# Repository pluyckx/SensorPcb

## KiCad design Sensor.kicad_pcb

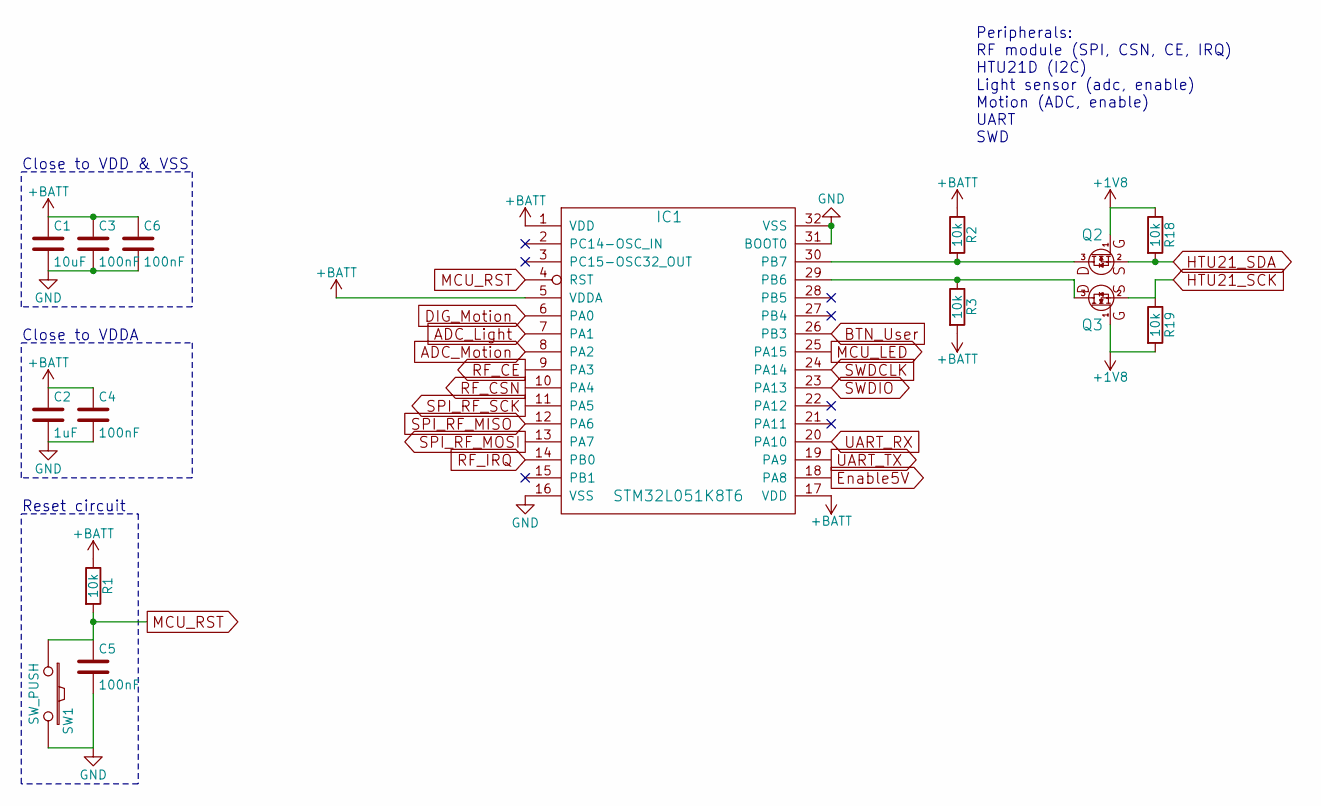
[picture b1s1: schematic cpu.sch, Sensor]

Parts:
C1: 10uF; R_0805
C2: 1uF; R_0805
C3, C4, C5, C6: 100nF; R_0805
IC1: STM32L051K8T6; STM32L051-LQFP32
Q2, Q3: NMosfetGen; SOT23
R1, R2, R3, R18, R19: 10k; R_0603
SW1: SW_PUSH; MicroSwitch_6x6mm

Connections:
+1V8: Q2.1, Q3.1, R18.1, R19.2; also elsewhere on the board
+BATT: C1.1, C2.1, C3.1, C4.1, C6.1, IC1.1 (VDD), IC1.5 (VDDA), IC1.17 (VDD), R1.1, R2.1, R3.2; also elsewhere on the board
ADC_Light: IC1.7 (PA1); also elsewhere on the board
ADC_Motion: IC1.8 (PA2); also elsewhere on the board
BTN_User: IC1.26 (PB3); also elsewhere on the board
DIG_Motion: IC1.6 (PA0); also elsewhere on the board
Enable5V: IC1.18 (PA8); also elsewhere on the board
GND: C1.2, C2.2, C3.2, C4.2, C5.2, C6.2, IC1.16 (VSS), IC1.31 (BOOT0), IC1.32 (VSS), SW1.2; also elsewhere on the board
HTU21_SCK: Q3.2, R19.1; also elsewhere on the board
HTU21_SDA: Q2.2, R18.2; also elsewhere on the board
MCU_LED: IC1.25 (PA15); also elsewhere on the board
MCU_RST: C5.1, IC1.4 (RST), R1.2, SW1.1; also elsewhere on the board
unnamed: IC1.29 (PB6), Q3.3, R3.1
unnamed: IC1.30 (PB7), Q2.3, R2.2
RF_CE: IC1.9 (PA3); also elsewhere on the board
RF_CSN: IC1.10 (PA4); also elsewhere on the board
RF_IRQ: IC1.14 (PB0); also elsewhere on the board
SPI_RF_MISO: IC1.12 (PA6); also elsewhere on the board
SPI_RF_MOSI: IC1.13 (PA7); also elsewhere on the board
SPI_RF_SCK: IC1.11 (PA5); also elsewhere on the board
SWDCLK: IC1.24 (PA14); also elsewhere on the board
SWDIO: IC1.23 (PA13); also elsewhere on the board
UART_RX: IC1.20 (PA10); also elsewhere on the board
UART_TX: IC1.19 (PA9); also elsewhere on the board

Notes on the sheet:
Close to VDD & VSS
Close to VDDA
Reset circuit
Peripherals: RF module (SPI, CSN, CE, IRQ) HTU21D (I2C) Light sensor (adc, enable) Motion (ADC, enable) UART SWD

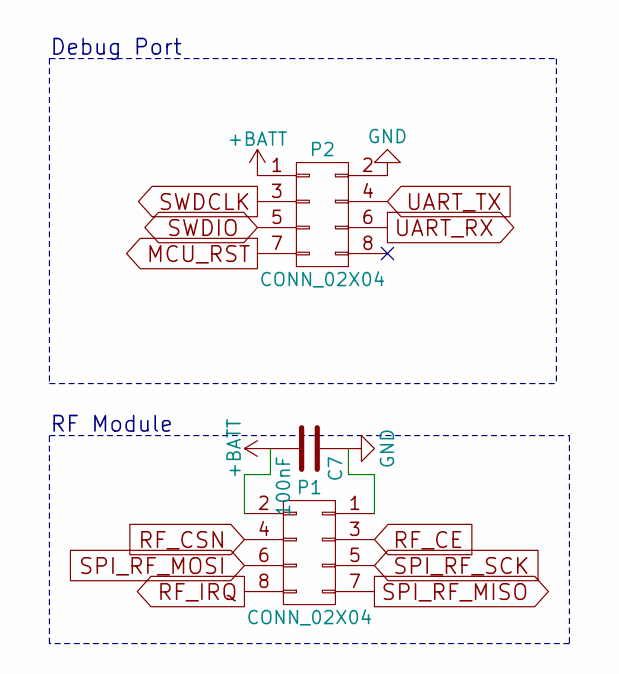
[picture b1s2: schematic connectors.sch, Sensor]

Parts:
C7: 100nF; R_0805
P1: CONN_02X04; Pin_Header_Straight_2x04_SMD
P2: CONN_02X04; Pin_Header_Straight_2x04_TH

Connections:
+BATT: C7.2, P1.2, P2.1; also elsewhere on the board
GND: C7.1, P1.1, P2.2; also elsewhere on the board
MCU_RST: P2.7; also elsewhere on the board
RF_CE: P1.3; also elsewhere on the board
RF_CSN: P1.4; also elsewhere on the board
RF_IRQ: P1.8; also elsewhere on the board
SPI_RF_MISO: P1.7; also elsewhere on the board
SPI_RF_MOSI: P1.6; also elsewhere on the board
SPI_RF_SCK: P1.5; also elsewhere on the board
SWDCLK: P2.3; also elsewhere on the board
SWDIO: P2.5; also elsewhere on the board
UART_RX: P2.6; also elsewhere on the board
UART_TX: P2.4; also elsewhere on the board

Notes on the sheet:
RF Module
Debug Port

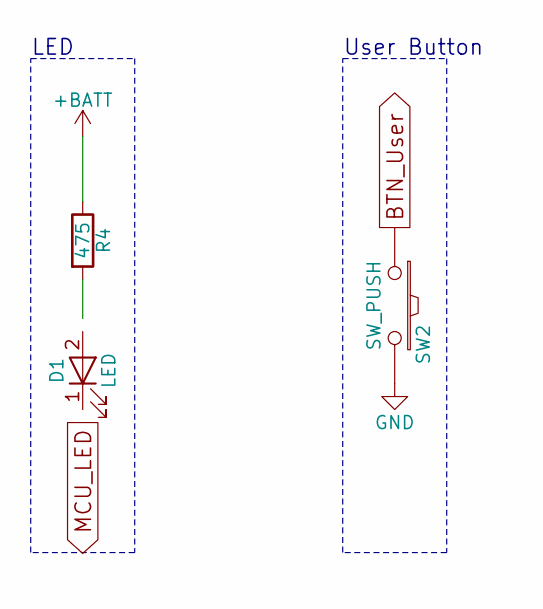
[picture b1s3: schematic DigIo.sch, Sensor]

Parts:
D1: LED; R_1206
R4: 475; R_0603
SW2: SW_PUSH; MicroSwitch_6x6mm

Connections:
+BATT: R4.1; also elsewhere on the board
BTN_User: SW2.1; also elsewhere on the board
GND: SW2.2; also elsewhere on the board
MCU_LED: D1.1 (K); also elsewhere on the board
unnamed: D1.2 (A), R4.2

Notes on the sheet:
LED
User Button

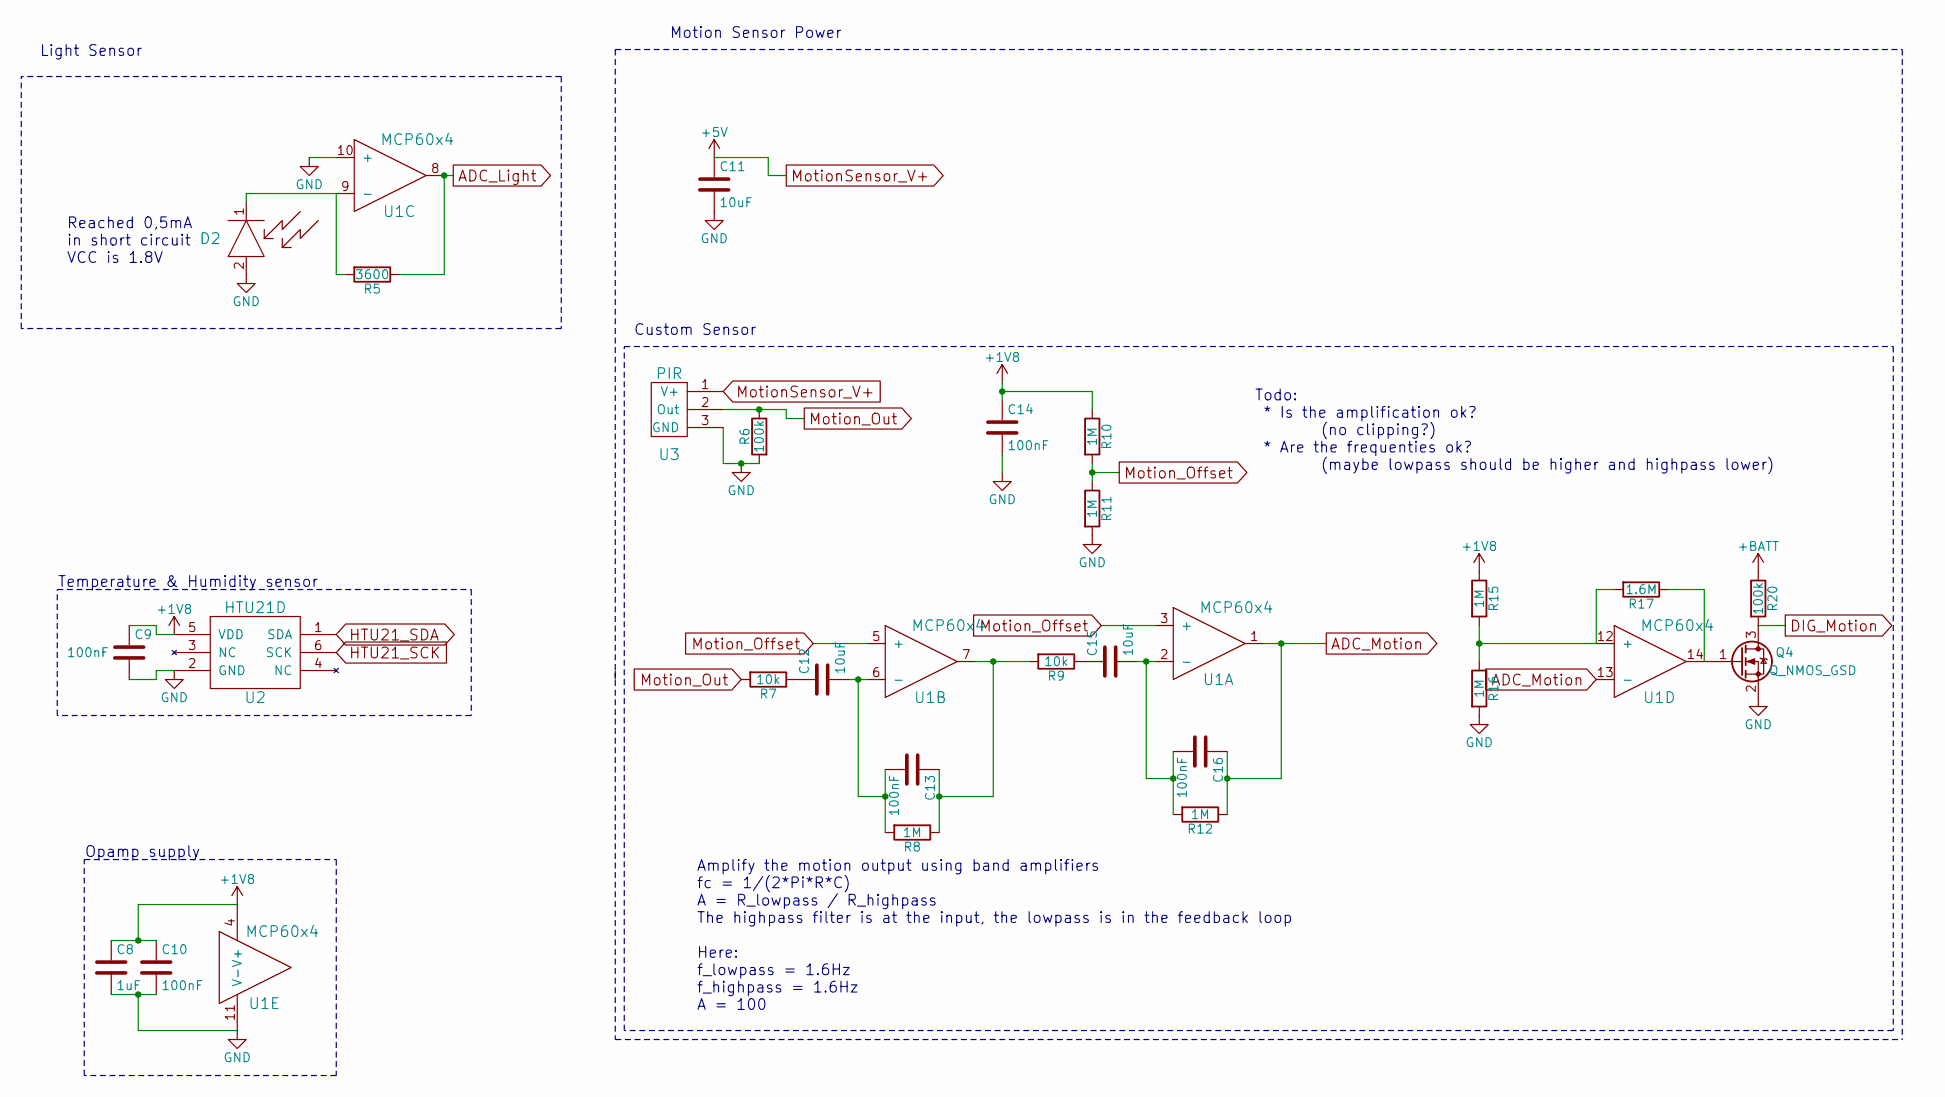
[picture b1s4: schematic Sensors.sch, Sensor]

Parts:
C8: 1uF; R_0805
C9, C10, C13, C14, C16: 100nF; R_0805
C11, C12, C15: 10uF; R_0805
D2: PhotoDiode; PD638C
Q4: Q_NMOS_GSD; SOT23
R5: 3600; R_0603
R6, R20: 100k; R_0603
R7, R9: 10k; R_0603
R8, R10, R11, R12, R15, R16: 1M; R_0603
R17: 1.6M; R_0603
U1: MCP60x4; SOIC-14
U2: HTU21D; HTU21D_QFN
U3: PIR

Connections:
+1V8: C8.1, C9.1, C10.1, C14.1, R10.1, R15.1, U1.4 (V+), U2.5 (VDD); also elsewhere on the board
+BATT: R20.1; also elsewhere on the board
ADC_Light: R5.1, U1.8; also elsewhere on the board
ADC_Motion: C16.1, R12.1, U1.1, U1.13 (-); also elsewhere on the board
DIG_Motion: Q4.3 (D), R20.2; also elsewhere on the board
GND: C8.2, C9.2, C10.2, C11.2, C14.2, D2.2, Q4.2 (S), R6.2, R11.2, R16.2, U1.10 (+), U1.11 (V-), U2.2 (GND), U3.3 (GND); also elsewhere on the board
HTU21_SCK: U2.6 (SCK); also elsewhere on the board
HTU21_SDA: U2.1 (SDA); also elsewhere on the board
MotionSensor_V+: C11.1, U3.1 (V+); also elsewhere on the board
Motion_Offset: R10.2, R11.1, U1.3 (+), U1.5 (+)
Motion_Out: R6.1, R7.2, U3.2 (Out)
unnamed: C12.1, R7.1
unnamed: C12.2, C13.2, R8.2, U1.6 (-)
unnamed: C13.1, R8.1, R9.2, U1.7
unnamed: C15.1, R9.1
unnamed: C15.2, C16.2, R12.2, U1.2 (-)
unnamed: D2.1, R5.2, U1.9 (-)
unnamed: Q4.1 (G), R17.1, U1.14
unnamed: R15.2, R16.1, R17.2, U1.12 (+)

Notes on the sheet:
Motion Sensor Power
Custom Sensor
Light Sensor
Amplify the motion output using band amplifiers fc = 1/(2*Pi*R*C) A = R_lowpass / R_highpass The highpass filter is at the input, the lowpass is in the feedback loop Here: f_lowpass = 1.6Hz f_highpass = 1.6Hz A = 100
Todo: * Is the amplification ok? (no clipping?) * Are the frequenties ok? (maybe lowpass should be higher and highpass lower)
Reached 0,5mA in short circuit VCC is 1.8V
Temperature & Humidity sensor
Opamp supply

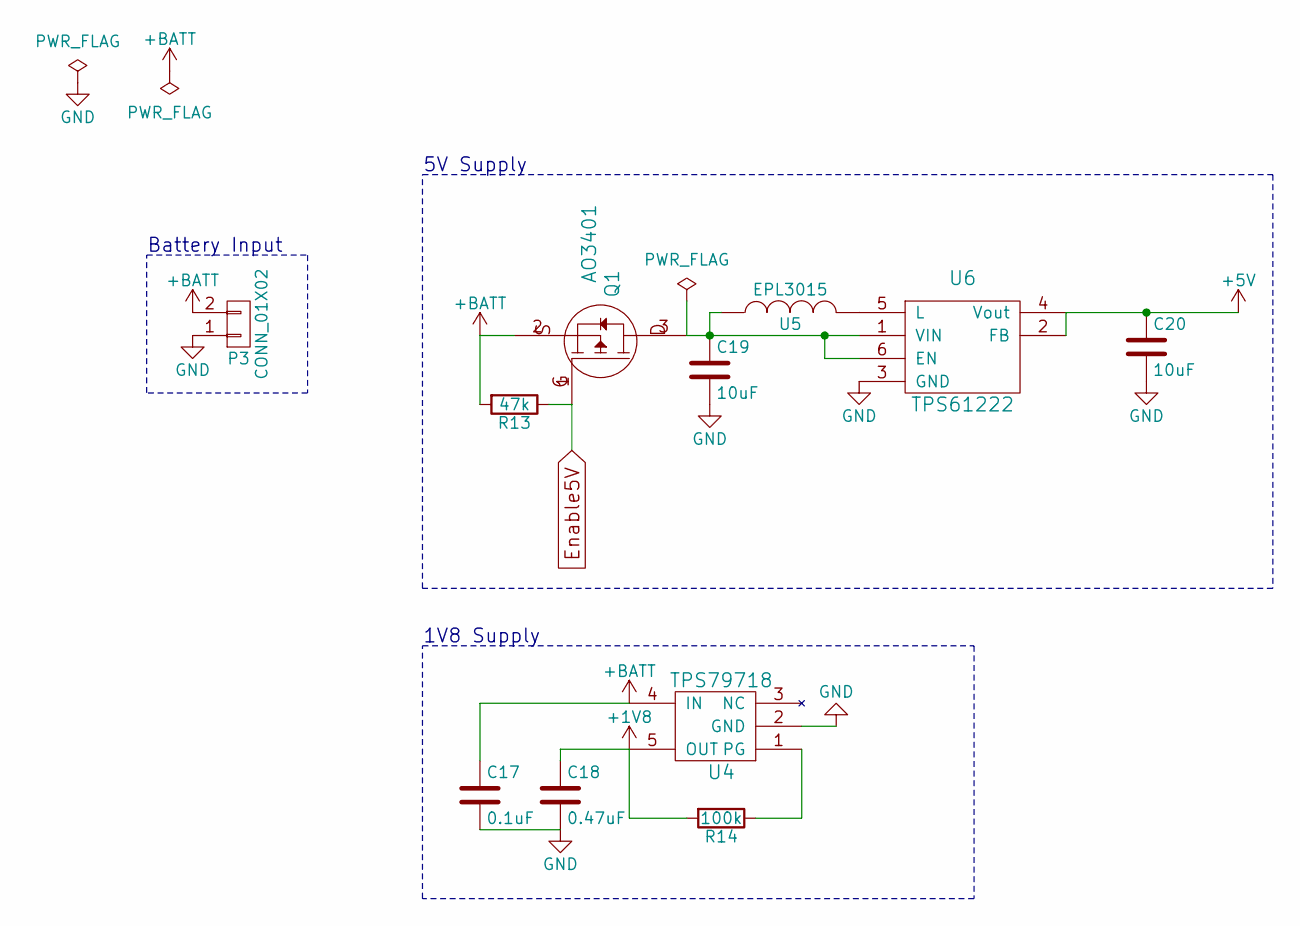
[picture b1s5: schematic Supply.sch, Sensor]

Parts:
C17: 0.1uF; R_0805
C18: 0.47uF; R_0805
C19, C20: 10uF; R_0805
P3: CONN_01X02; ConnWago_2059_2P_SMD
Q1: AO3401; SOT23
R13: 47k; R_0603
R14: 100k; R_0603
U4: TPS79718; SC70
U5: EPL3015
U6: TPS61222; TPS6122x

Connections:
+1V8: C18.1, R14.2, U4.5 (OUT); also elsewhere on the board
+BATT: C17.1, P3.2, Q1.2, R13.2, U4.4 (IN); also elsewhere on the board
Enable5V: Q1.1, R13.1; also elsewhere on the board
GND: C17.2, C18.2, C19.2, C20.2, P3.1, U4.2 (GND), U6.3 (GND); also elsewhere on the board
MotionSensor_V+: C20.1, U6.2 (FB), U6.4 (Vout); also elsewhere on the board
unnamed: C19.1, Q1.3, U5.1, U6.1 (VIN), U6.6 (EN)
unnamed: R14.1, U4.1 (PG)
unnamed: U5.2, U6.5 (L)

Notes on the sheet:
Battery Input
5V Supply
1V8 Supply

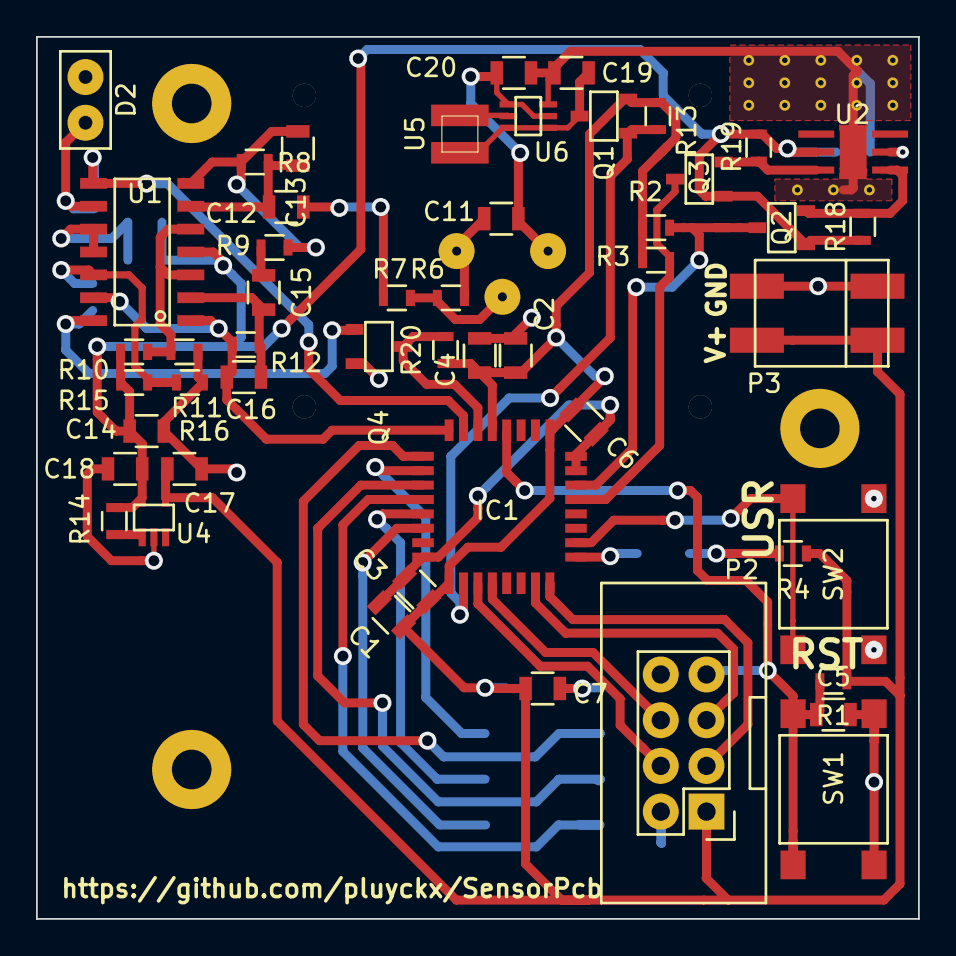
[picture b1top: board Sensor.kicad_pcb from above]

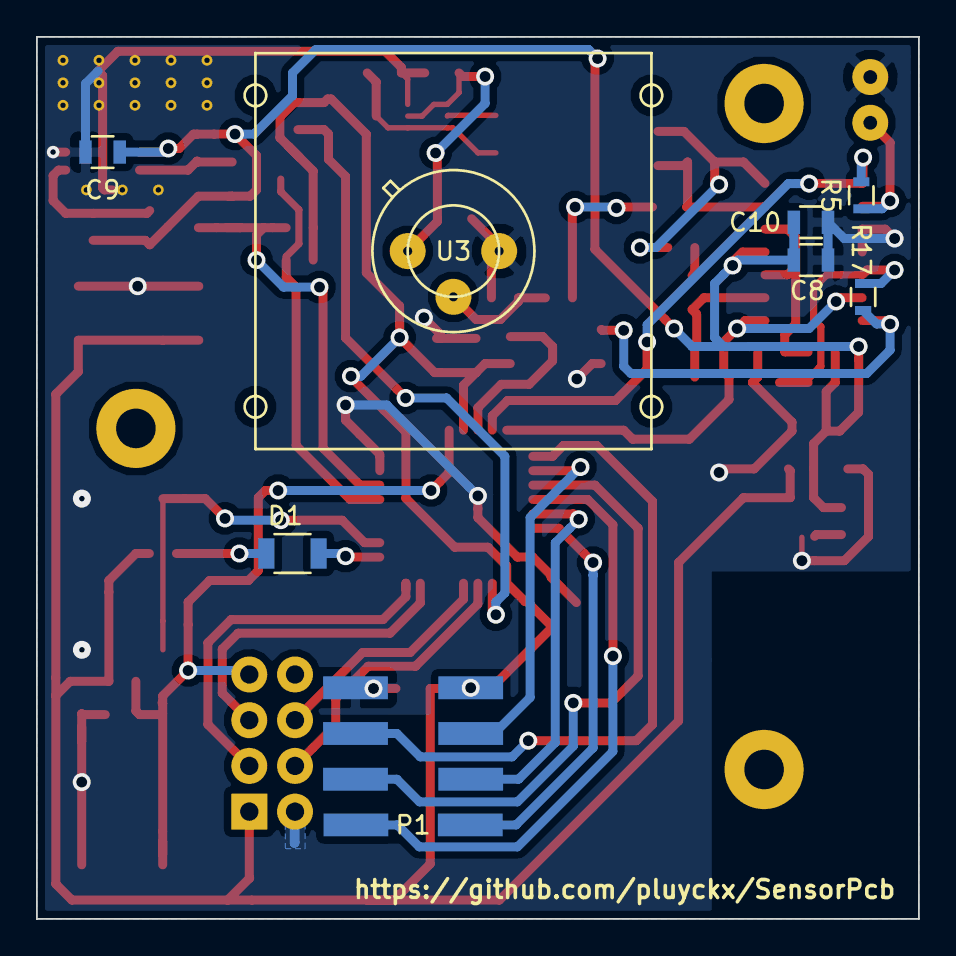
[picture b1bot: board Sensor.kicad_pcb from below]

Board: 2 copper layers, 49.0 x 49.0 mm, 58 parts (8 on the bottom side), 39 nets.

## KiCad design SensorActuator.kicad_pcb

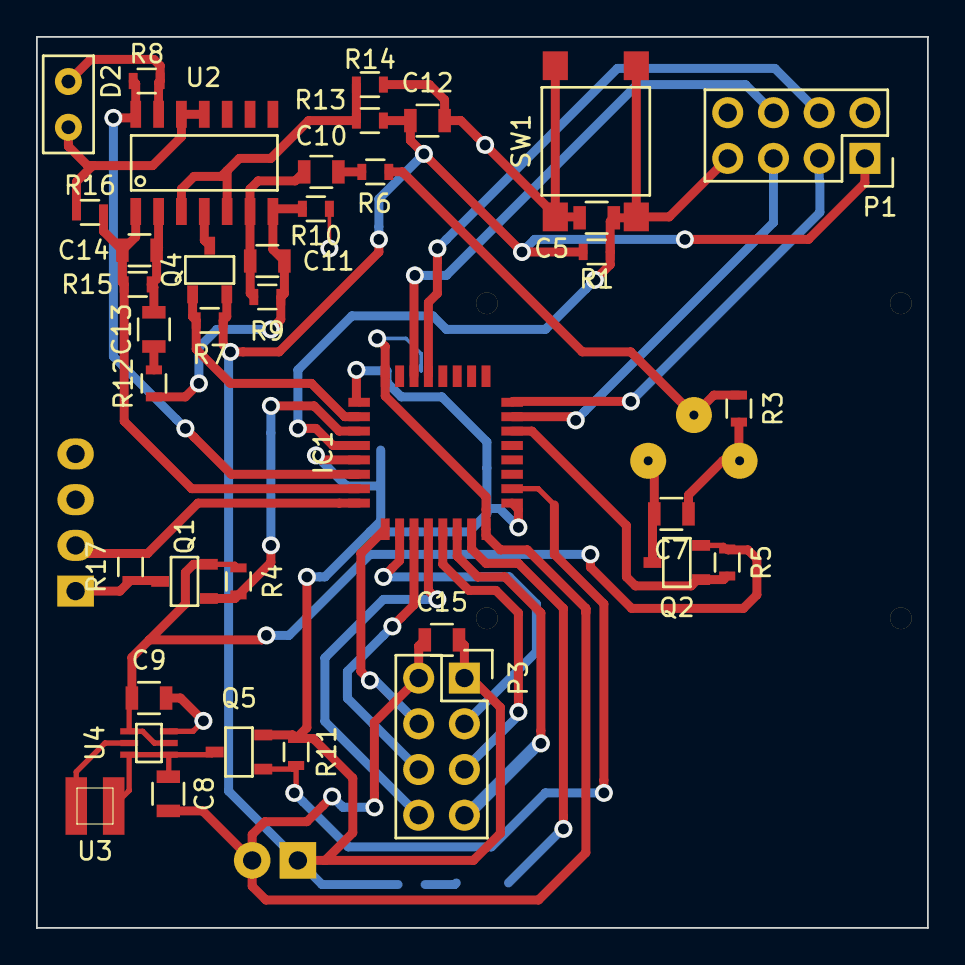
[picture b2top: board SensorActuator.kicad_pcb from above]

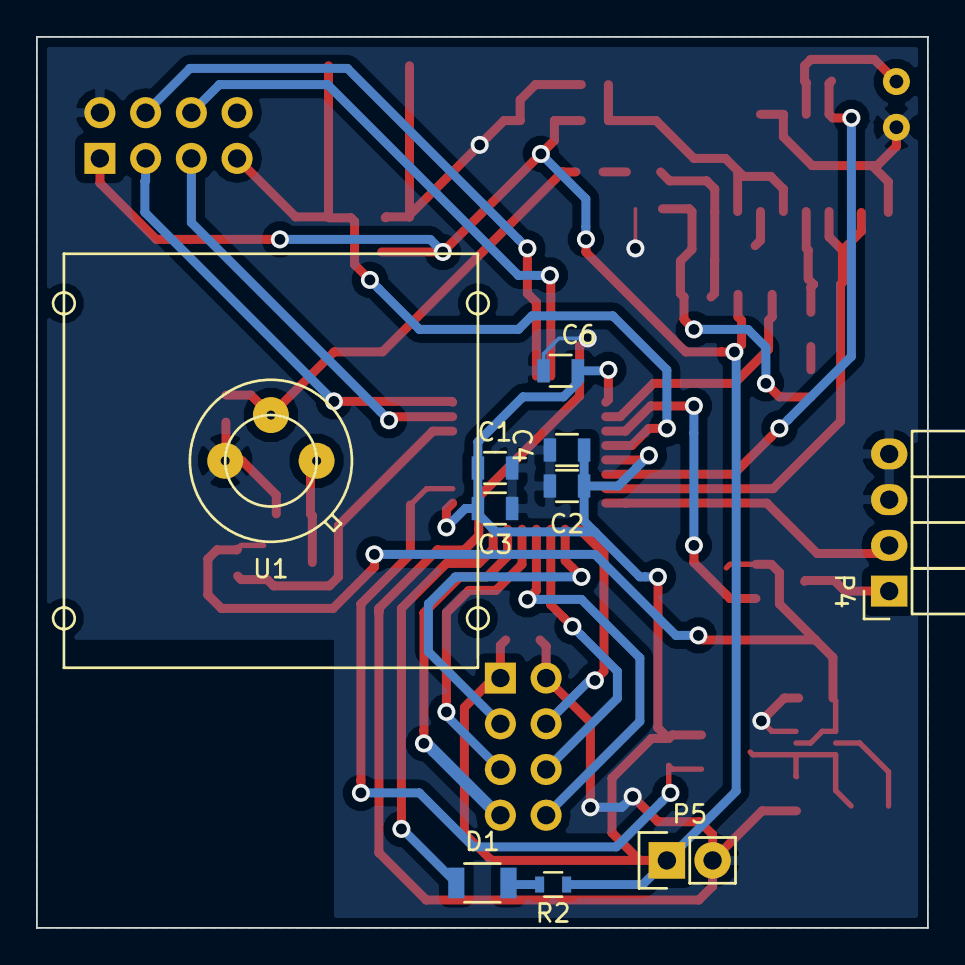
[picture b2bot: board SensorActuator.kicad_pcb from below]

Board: 2 copper layers, 49.5 x 49.5 mm, 48 parts (10 on the bottom side), 36 nets.

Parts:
C1, C7, C8, C9, C10, C13: 10uF; R_0805
C2: 1uF; R_0805
C3, C4, C5, C6, C11, C14: 100nF; R_0805
C12, C15: C; R_0805
D1: LED; R_1206
D2: PhotoDiode; PD638C
IC1: STM32L051K8T6; STM32L051-LQFP32
P1, P3: CONN_02X04; Socket_Strip_Straight_2x04
P4: CONN_01X04; Socket_Strip_Angled_1x04
P5: CONN_01X02; Socket_Strip_Straight_1x02
Q1, Q2, Q4: PMosfetGen; SOT23
Q5: AO3401; SOT23
R1, R3, R13, R14: 100k; R_0603
R2: 475; R_0603
R4, R5, R7: 47.5k; R_0603
R6, R10, R12, R16: 10k; R_0603
R8: 3600; R_0603
R9, R15: 1M; R_0603
R11: 47k; R_0603
R17: 1k; R_0603
SW1: SW_PUSH; MicroSwitch_6x6mm
U1: PIR
U2: MCP6004; SOIC-14
U3: EPL3015
U4: TPS61222; TPS6122x

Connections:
+5V: C9.1, Q1.2, Q2.2, R4.1, R5.1, U4.2, U4.4
+BATT: C1.1, C2.1, C3.1, C4.1, C6.1, C12.1, C15.2, IC1.1, IC1.5, IC1.17, P1.1, P3.1, P5.1, Q4.2, Q5.2, R1.1, R2.1, R7.1, R11.2, R13.1
ADC_Light: IC1.6, R8.1, U2.14
ADC_Motion: C14.1, IC1.7, R15.1, R16.1, U2.1
DHT22_Enable: IC1.3, Q1.1, R4.2
Enable5V: IC1.18, Q5.1, R11.1
GND: C1.2, C2.2, C3.2, C4.2, C5.2, C6.2, C7.2, C8.2, C9.2, C12.2, C15.1, D2.2, IC1.16, IC1.32, P1.2, P3.2, P4.3, P4.4, P5.2, R3.2, R10.2, R14.2, R16.2, SW1.2, U1.3, U2.11, U2.12, U4.3
MCU_LED: D1.1, IC1.15
MCU_RST: C5.1, IC1.4, P1.7, R1.2, SW1.1
MotionSens_Enable: IC1.22, Q2.1, R5.2
MotionSensor_V+: C7.1, Q2.3, U1.1
Motion_Offset: R13.2, R14.1, U2.3, U2.5
Motion_Out: R3.1, R6.2, U1.2
unnamed: C8.1, Q5.3, U3.1, U4.1, U4.6
unnamed: C10.1, R6.1
unnamed: C10.2, C11.2, R9.2, U2.6
unnamed: C11.1, R9.1, R10.1, R12.2, U2.7
unnamed: C13.1, R12.1
unnamed: C13.2, C14.2, R15.2, U2.2
unnamed: D1.2, R2.2
unnamed: D2.1, R8.2, U2.13
unnamed: P4.1, Q1.3, R17.1
unnamed: U3.2, U4.5
OpampEnable: IC1.2, Q4.1, R7.2
Opamp_V+: Q4.3, U2.4
RF_CE: IC1.9, P3.4
RF_CSN: IC1.10, P3.3
RF_IRQ: IC1.14, P3.7
SPI_RF_MISO: IC1.12, P3.8
SPI_RF_MOSI: IC1.13, P3.5
SPI_RF_SCK: IC1.11, P3.6
SWDCLK: IC1.24, P1.3
SWDIO: IC1.23, P1.5
Temp_1Wire: IC1.8, P4.2, R17.2
UART_RX: IC1.30, P1.6
UART_TX: IC1.29, P1.4

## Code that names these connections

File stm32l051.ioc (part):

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Mcu.Name=STM32L051K(6-8)Tx
Mcu.Package=LQFP32
Mcu.UserName=STM32L051K8Tx
PA0.GPIOParameters=GPIO_Label
PA0.GPIO_Label=LightAdc
PA0.Mode=IN0
PA0.Signal=ADC_IN0
PA1.GPIOParameters=GPIO_Label
PA1.GPIO_Label=MotionAdc
PA1.Mode=IN1
PA1.Signal=ADC_IN1
PA10.Mode=Asynchronous
PA10.Signal=USART1_RX
PA13.Mode=Serial_Wire
PA13.Signal=SYS_SWDIO
PA14.Mode=Serial_Wire
PA14.Signal=SYS_SWCLK
PA15.GPIOParameters=GPIO_Label
PA15.GPIO_Label=Led
PA15.Signal=GPIO_Output
PA3.GPIOParameters=GPIO_Label
PA3.GPIO_Label=RfCe
PA3.Signal=GPIO_Output
PA4.Mode=NSS_Signal_Hard_Input
PA4.Signal=SPI1_NSS
PA5.GPIOParameters=GPIO_Label
PA5.GPIO_Label=RfSck
PA5.Mode=Full_Duplex_Master
PA5.Signal=SPI1_SCK
PA6.GPIOParameters=GPIO_Label
PA6.GPIO_Label=RfMiso
PA6.Mode=Full_Duplex_Master
PA6.Signal=SPI1_MISO
PA7.GPIOParameters=GPIO_Label
PA7.GPIO_Label=RfMosi
PA7.Mode=Full_Duplex_Master
PA7.Signal=SPI1_MOSI
PA8.GPIOParameters=GPIO_Label
PA8.GPIO_Label=5VEnable
PA8.Signal=GPIO_Output
PA9.Mode=Asynchronous
PA9.Signal=USART1_TX
PB0.GPIOParameters=GPIO_Label
PB0.GPIO_Label=RfIrq
PB0.Signal=GPIO_Input
PB6.GPIOParameters=GPIO_Label
PB6.GPIO_Label=HTU21_SCK
PB6.Mode=I2C
PB6.Signal=I2C1_SCL
PB7.GPIOParameters=GPIO_Label
PB7.GPIO_Label=HTU21_SDA
PB7.Mode=I2C
PB7.Signal=I2C1_SDA
RCC.SYSCLKFreq_VALUE=2097000

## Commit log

2015-12-11 Initial version of sensor pcb
2015-12-11 Version 2 of the pcb
    * PCB is now exact 50x38 mm, so we can print it on a small board
    * Through hole components have only a pad on one side,
    this way we are sure we connect the correct pad
2015-12-11 Add drill holes
2015-12-11 Remove VCC from UART-DBG connector
    * VCC of a USB-TTL connector may not be connected to VCC of the board.
    The usb will put 3.3V (or 5V) on this pin, so we will create a short
    circuit if we connect the TLL and use a battery as supply.
2015-12-13 Increase clearance for fill zones to 0.4mm
2015-12-13 Fix a 5V trace
2015-12-13 Prepare for release V1
2015-12-31 Created some more outputs of V1
2015-12-31 Correct some schematics and add todos on pcb
2016-01-24 Add Opamp circuit
    * Amplify the output of the motion sensor using a AC coupled band
    amplifier.
    * Use one of the opamp circuits as a voltage follower for the light
    sensor to limit the output to 0V and VCC.
2016-02-12 Update schematic and reroute print
    * Update opamp circuit for light sensor
    * Change opamp
    * Reroute everything
2016-02-12 Use 0603 resistors
2016-02-14 Finalize pcb
    * Make pcb 50x50mm
    * Increase clearance for filled zones
2016-02-14 Add release files
2016-03-03 Update pull-up resistor for a sensor
2016-03-06 Finish work on V2
    * Rework layout
    * Reassign mcu pins
    * Add a capacitor for the RF module
2016-03-06 Only use one ground plane and reduce pcb size
2016-03-06 Remove previous output files
2016-03-06 Add some original library
2016-03-06 Correct some silks
2016-03-06 Rename project and generate output files
2016-03-06 Produce extra output files for V2
2016-03-12 Add M3 mounting holes
2016-03-16 Change texts for connectors and fix track width
2016-03-20 Fix Boot0 pin and add prices per component
2016-03-27 Fix Boot0 pin and mechanical problem with the Fresnel lens
    * Resistor at Boot0 pin not necessary:
    it is only input and can directly connected to ground
    * The capacitors above the cpu on the bottom layer are not
    correctly placed: there is a problem when placing the
    Fresnel lens.
2016-06-04 Update schematics for V3:
    * Change DHT22 to HTU21D
    * Change schematic for MCP6044
    * Correct unused opamp + power supply
    * Reassign some cpu pins (for HTU21D)
    * Add LDO power supply for 1.8V
    * Update STM32CubeMx project
2016-06-05 Updates for V3:
    * Remove unnecessary power supply enable MOSFETs
    * Optimize pin configuration
2016-06-10 Finish schematic, assign all footprints for V3
2016-06-26 Finish routing v4
2016-06-26 Add some docs
2016-07-22 Update some routing
2016-07-22 Add extra switch for user defined functionality
    * reroute pcb
2016-07-22 Remove backup files
2016-07-22 Update schematic pdf
2016-09-12 Add data files for pcb
2016-09-12 Remove unnecessary via
2016-09-15 Update QFN package for easier soldering
2017-02-05 Corrections I2C and Dig Opamp out
    * Fix level shift for I2C
    * Fix level shift opamp digital out (PIR)
2017-02-05 Add documentations for opamps
2017-02-12 Update connectors to custom ones
2017-02-17 Add prices
2017-02-17 Add docs for used mcu
2017-03-05 Update connector for Vin
2017-03-05 Make panelized pcb & generate gerbers
2017-03-08 Finish layout
2017-03-08 Add url to open source project on silkscreens
2017-03-08 Use correct generated files for seeedstudio
2017-04-18 Add last changes and gerber files
2017-04-18 Add description of debug connector pinout
2017-04-18 update documentation pinout
